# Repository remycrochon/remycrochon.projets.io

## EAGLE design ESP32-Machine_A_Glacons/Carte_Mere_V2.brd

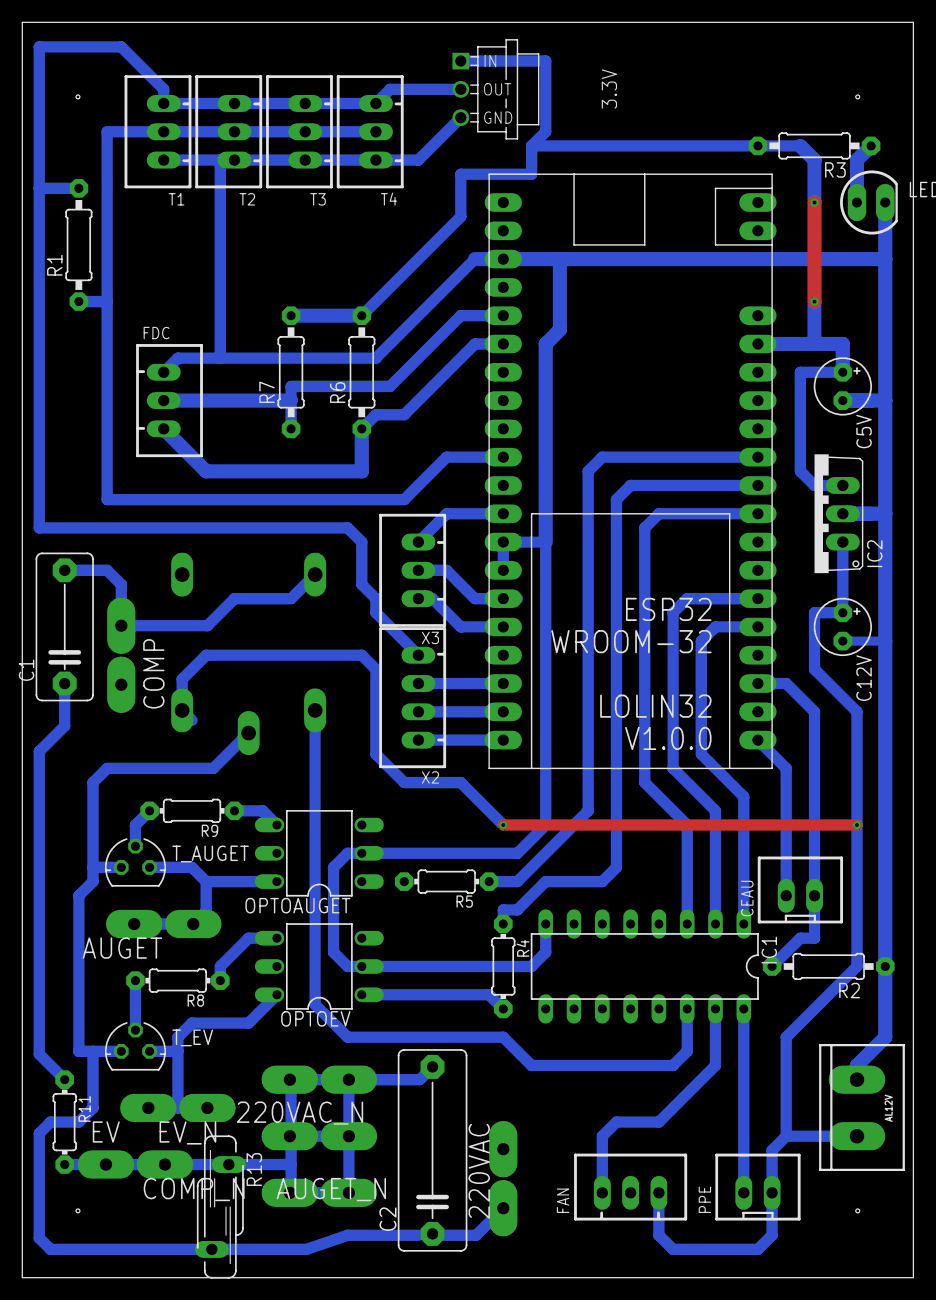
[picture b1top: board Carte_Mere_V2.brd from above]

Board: 2 copper layers, 80.0 x 112.7 mm, 44 parts (1 on the bottom side), 37 nets.

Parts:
3.3V: REG-AMS1117-3P-3.3V#V; REG-AMS1117-3P#V
220VAC, 220VAC_N: PIN2F061.040; F061.040
AL12V: BORNIER_A_VIS_2_5.12MM
AUGET: PIN2F061.040; F061.040
AUGET_N: PIN2F061.040; F061.040
C1: 47nF; C10B5
C2: 0.1µF; C15B6
C5V, C12V: 47µF; E2,5-5
CEAU: JST-XH-02-PIN-LONG-PAD; JST-XH-02-PACKAGE-LONG-PAD
COMP: PIN2F061.040; F061.040
COMP_N: PIN2F061.040; F061.040
EV: PIN2F061.040; F061.040
EV_N: PIN2F061.040; F061.040
FAN: JST-XH-03-PIN-LONG-PAD; JST-XH-03-PACKAGE-LONG-PAD
FDC: JST-XH-03-PIN-LONG-PAD; JST-XH-03-PACKAGE-LONG-PAD
IC1: ULN2003AN; DIL16
IC2: 7805TV; TO220V
LED1: LED5MM
OPTOAUGET: MOC3041M; DIL06
OPTOEV: MOC3041M; DIL06
PPE: JST-XH-02-PIN-LONG-PAD; JST-XH-02-PACKAGE-LONG-PAD
R1, R6, R7: 4.7K; 0207/10
R2: 10K; 0207/10
R3: 330R; 0207/10
R4, R5, R8, R9, R11: 220R; 0204/7
R13: S10K11
R_COMP: G5L; G5LE
T1, T2, T3, T4: JST-XH-03-PIN-LONG-PAD; JST-XH-03-PACKAGE-LONG-PAD
T_AUGET: TRIAC_TO92-1; TO92-6
T_EV: TRIAC_TO92-1; TO92-6
U$1: ESP32_LOLIN_V1.0.0
X2: JST-XH-04-PIN-LONG-PAD; JST-XH-04-PACKAGE-LONG-PAD
X3: JST-XH-03-PIN-LONG-PAD; JST-XH-03-PACKAGE-LONG-PAD

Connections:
0V: 3.3V.3, AL12V.1, C5V.V-, C12V.V-, FDC.1, IC1.8, IC2.2, LED1.K, OPTOAUGET.2, OPTOEV.2, R2.1, T1.1, T2.1, T3.1, T4.1, U$1.23, U$1.24, U$1.34
3.3V: CEAU.1, U$1.1
3V3: U$1.20, U$1.29
+5V: 3.3V.1, C5V.V+, IC2.3, R3.2, R6.2, R7.2, U$1.15
+12V: AL12V.2, C12V.V+, FAN.3, IC2.1, PPE.2, R_COMP.1
unnamed: U$1.21, X3.1
unnamed: EV.A1, EV.A2, OPTOEV.6, T_EV.A2
unnamed: IC1.1, U$1.5
unnamed: FDC.2, R7.1, U$1.32
unnamed: IC1.2, U$1.6
unnamed: C1.1, R11.1
unnamed: LED1.A, R3.1
unnamed: IC1.16, PPE.1
unnamed: FAN.1, IC1.15
unnamed: IC1.14, R_COMP.2
unnamed: IC1.3, U$1.9
unnamed: R4.1, U$1.10
unnamed: R5.1, U$1.11
unnamed: OPTOEV.1, R4.2
unnamed: AUGET.A1, AUGET.A2, OPTOAUGET.6, T_AUGET.A2
unnamed: U$1.22, X3.2
unnamed: OPTOEV.4, R8.1
unnamed: C1.2, COMP.A1, COMP.A2, R_COMP.O
unnamed: OPTOAUGET.1, R5.2
unnamed: U$1.17, X2.1
unnamed: FDC.3, R6.1, U$1.31
unnamed: U$1.18, X2.2
unnamed: U$1.19, X2.3
unnamed: U$1.25, X3.3
unnamed: CEAU.2, R2.2, U$1.3
unnamed: OPTOAUGET.4, R9.1
unnamed: R1.1, T1.2, T2.2, T3.2, T4.2, U$1.27
unnamed: R8.2, T_EV.G
unnamed: R9.2, T_AUGET.G
unnamed: 220VAC.A1, 220VAC.A2, C2.1, R13.2, R_COMP.P, T_AUGET.A1, T_EV.A1
unnamed: 220VAC_N.A1, 220VAC_N.A2, AUGET_N.A1, AUGET_N.A2, C2.2, COMP_N.A1, COMP_N.A2, EV_N.A1, EV_N.A2, R11.2, R13.1
VCC: 3.3V.2, R1.2, T1.3, T2.3, T3.3, T4.3, X2.4

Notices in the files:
parts and their libraries:
05-arduino_etc: Released under the Creative Commons Attribution 4.0 International License: http://creativecommons.org/licenses/by/4.0
